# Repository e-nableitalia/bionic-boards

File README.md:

# enable-it Bionic Boards - Third iteration

**This project is part of e-Nable.it Bionic Platform**

An open-source project for developing prosthetic and assistive devices through frugal innovation, designed to be part of e-Nable's open-source prosthetics. The project focuses on building electronic solutions that enable mechanical devices to achieve advanced functionalities, enhancing the community's designs with sophisticated, human-integrated electronic control while maintaining simplicity, affordability, and accessibility.

This project is developed and maintained by the volunteers of the e-Nable Italia community. Our group consists of passionate individuals, including biomedical engineers, mechatronics engineers, and makers, who collaborate to create innovative and accessible solutions. Through our collective efforts, we aim to empower users with open-source, affordable, and customizable assistive devices.

Additional details and information about the **e-nable.it Bionic Platform** can be found in [e-nable.it Bionic Plaform Wiki](https://dev.e-nableitalia.it/wiki/spaces/enableit/pages/360468/Bionic+Workgroup).

# Project roadmap

The project unfolds in three development iterations, each aimed at validating, prototyping, and engineering innovative solutions for low-cost bionic devices.

1. Ideas Validation
The first phase involves conducting experiments and tests to validate initial ideas. This phase focuses on identifying the most promising solutions, exploring various options for controlling actuators and sensors, and collecting data to establish guidelines for the prototype.

2. Prototyping & Custom Solutions
During the prototyping phase, custom solutions are developed using commercial components integrated with specialized electronic boards. The most promising ideas are implemented into physical prototypes to validate architectural and structural concepts. The focus is on simplicity and reliability, ensuring the solutions can be easily replicated and adapted for various bionic devices.

3. Frugal Innovation Engineering
The final phase focuses on engineering the solutions based on frugal innovation principles. Prototypes are optimized to make them accessible, scalable, and practical, with a strong emphasis on cost-effectiveness and real-world applicability. The engineering process also involves creating an open-source hardware platform that enables the creation of modular systems easily combined to build bionic devices.

This repository relates to Iteration #3.

The objective of this iteration is to develop the first reusable deliverables of the project, a set of electronic modules that empower mechanical devices with advanced functionalities. 

By integrating sophisticated, human-centered electronic control, we strive to enhance the capabilities of the e-Nable community's designs while ensuring they remain simple, affordable, and accessible.

> [!CAUTION]
> **The boards published in this repository are still under development and, until fully completed and thoroughly validated, they are intended solely as technological demonstrators and are not designed for practical use.**

## Initial Release Boards

This initial release includes the following boards:

**1. Bionic Controller**  
The Bionic Controller is a custom control board designed to house and expand the capabilities of the M5Stack Atom S3 board. It connects seamlessly to its daughter boards via an 8+8 pin expansion slot.

**This module serves as the foundation for flexible, low-cost prosthetic and assistive device applications.**

Key features:  
- **Size:** 25x50mm  
- **Layers:** 2-layer board  
- **Power Management:** Provides battery management and charging, delivering three power outputs (+3.3V, +5V, and a variable voltage between 5V and 12V for powering multiple motors simultaneously).  
- **Expansion Slot:** Includes a 8+8 pin expansion slot for a daughter board.  
- **Housing:** Designed to house the [M5Stack Atom S3](https://docs.m5stack.com/en/core/AtomS3) board.  

Latest version:
- **Files:** Atom S3 Module Rev. D

**2. ActuatorSense Module**  
The ActuatorSense module is a compact, low-cost H-bridge/waveshare motor controller daughter board designed to connect seamlessly to the expansion slot of the Bionic Controller board.

Key features:  
- **Size:** 26x25mm  
- **Layers:** 2-layer board  
- **Capabilities:**  
  - Can control up to two linear actuators (or two motors).
  - Can control waveshare servo/motors  
  - Supports a combination of one actuator/motor and one sensor (myoelectric or pressure). 

Latest version:
- **Files:** DRV8441A Module Rev B  

**3. Advanced Control Board**  
An enhanced version of the basic control board with added features (not yet released):  
- Includes three slots for daughter boards, enabling control of multiple actuators.  
- Retains all capabilities of the Bionic Controller.  

**4. Daughter Board with TI ADS1298**  
A specialized board for EMG signal acquisition (previous version prototype available):  
- **Functionality:** Designed to acquire up to eight simultaneous myoelectric signals.

## Project updates
250110 - Initial file upload

250113 - Updated to latest release, changes:
- fixed mechanical issue (wrong housing position for Atom S3 board, moved the connectors 4.5 mm below)
- reworked board polygons (cleaner design)
- completed 3d board models
- replaced single pin 2.54 headers with wirepad

250724 - Updated to latest release (DRV8441A Module Rev B), changes:
- tilted pin order on Actuonix PQ12 connector (J-A1 & J-A2 pin order need to be inverted because the connector has contacts on the opposite side)
- added waveshare driver logic and connector (1 wire data + GND + PWR)
- added a digital switch to enable waveshare (default) or additional h-bridge control (2nd motor)
- fixed ADC/Digital Atom S3 pin swap error (G38 & G39 cannot be used as ADC)

## KNOWN ISSUES

- Waveshare connector pinout is tilter: **Pin 1 is connected to Pin 3, and Pin 3 is connected to Pin 1**. Double-check wiring before connecting.

## Authors

Alberto Navatta - alberto@e-nableitalia.it / alberto.navatta@gmail.com

e-Nable Italia - info@e-nableitalia.it

Check for further information, updates and information on this and other e-Nable Italia’s projects on our website: [https://e-nableitalia.it/](https://e-nableitalia.it/)

## License

This material is released under *Creative Commons - Attribution - Non-Commercial - Share Alike license*

## LIMITATION OF LIABILITY.
UNDER NO CIRCUMSTANCES AND UNDER NO LEGAL THEORY, WHETHER TORT (INCLUDING NEGLIGENCE), CONTRACT, OR OTHERWISE, SHALL YOU, THE INITIAL DEVELOPER, ANY OTHER CONTRIBUTOR, OR ANY DISTRIBUTOR OF COVERED CODE, OR ANY SUPPLIER OF ANY OF SUCH PARTIES, BE LIABLE TO ANY PERSON FOR ANY INDIRECT, SPECIAL, INCIDENTAL, OR CONSEQUENTIAL DAMAGES OF ANY CHARACTER INCLUDING, WITHOUT LIMITATION, DAMAGES FOR LOSS OF GOODWILL, WORK STOPPAGE, COMPUTER FAILURE OR MALFUNCTION, OR ANY AND ALL OTHER COMMERCIAL DAMAGES OR LOSSES, EVEN IF SUCH PARTY SHALL HAVE BEEN INFORMED OF THE POSSIBILITY OF SUCH DAMAGES. THIS LIMITATION OF LIABILITY SHALL NOT APPLY TO LIABILITY FOR DEATH OR PERSONAL INJURY RESULTING FROM SUCH PARTY'S NEGLIGENCE TO THE EXTENT APPLICABLE LAW PROHIBITS SUCH LIMITATION. SOME JURISDICTIONS DO NOT ALLOW THE EXCLUSION OR LIMITATION OF INCIDENTAL OR CONSEQUENTIAL DAMAGES, SO THIS EXCLUSION AND LIMITATION MAY NOT APPLY TO YOU.

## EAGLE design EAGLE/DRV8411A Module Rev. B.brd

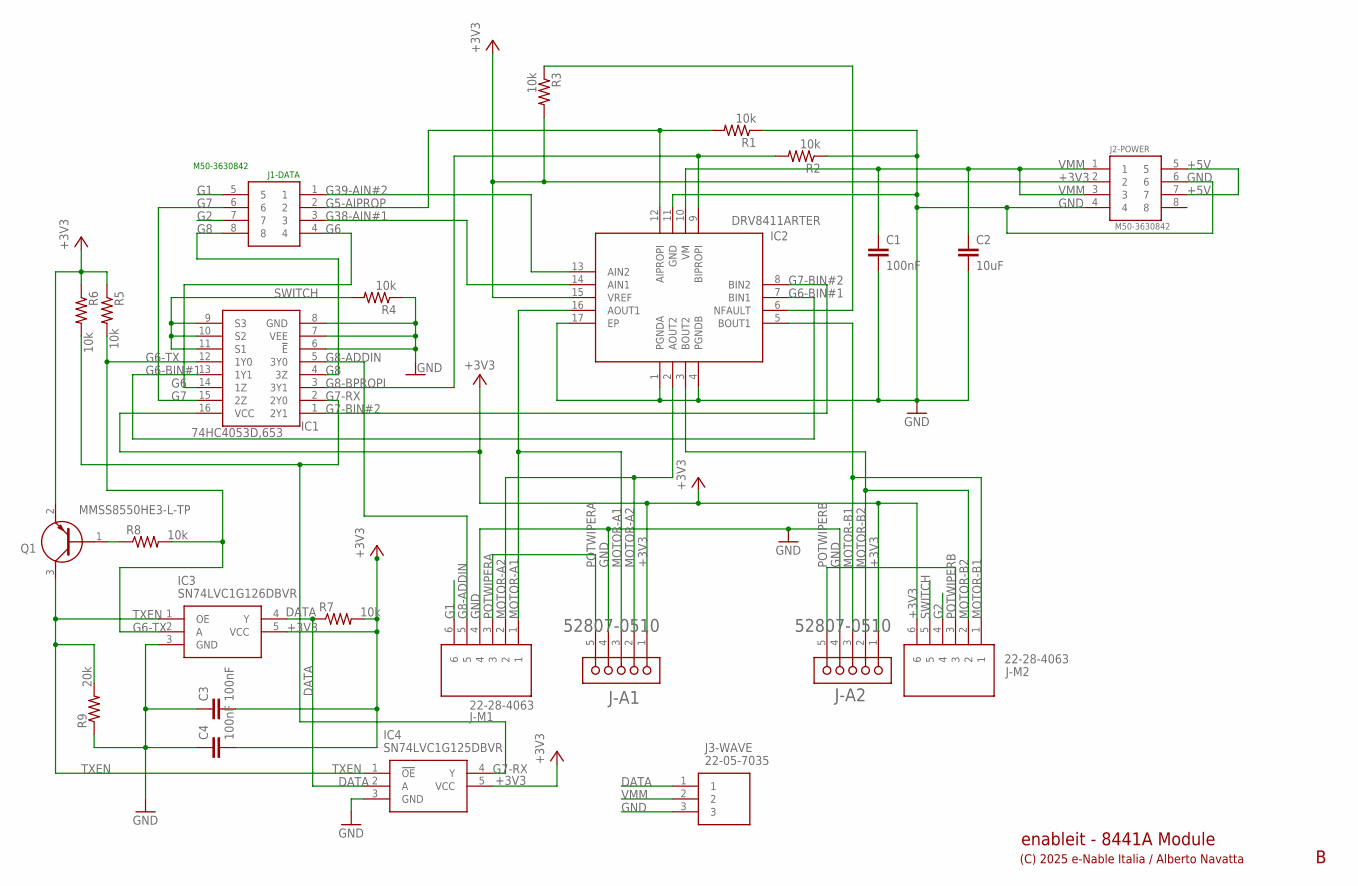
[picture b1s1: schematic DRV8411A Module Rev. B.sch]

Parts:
C1, C3, C4: 100nF; C0603
C2: 10uF; C1206
IC1: 74HC4053D,653; SOIC127P600X175-16N
IC2: DRV8411ARTER; QFN50P300X300X80-17N
IC3: SN74LVC1G126DBVR; SOT95P280X145-5N
IC4: SN74LVC1G125DBVR; SOT95P280X145-5N
J1-DATA, J2-POWER: M50-3630842; HUSRSP8W42P127_1016X210X430P
J3-WAVE: 22-05-7035; SHDRRA3W60P0X250_1X3_990X790X4
J-A1, J-A2: MOLEX_52807-0510MOLEX_52807-0510_0_0; MOLEX_52807-0510_0
J-M1, J-M2: 22-28-4063; HDRV6W66P0X254_1X6_1524X249X83
Q1: MMSS8550HE3-L-TP; SOT95P237X125-3N
R1, R2, R3, R4, R5, R6, R7, R8: 10k; R1206
R9: 20k; R1206

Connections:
+3V3: C3.2, C4.2, IC1.16 (VCC), IC2.15 (VREF), IC3.5 (VCC), IC4.5 (VCC), J2-POWER.2, J-A1.1, J-A2.1, J-M2.6, Q1.2 (E), R3.2, R5.1, R6.1, R7.2
+5V: J2-POWER.5, J2-POWER.7
DATA: IC3.4 (Y), IC4.2 (A), J3-WAVE.1, R7.1
G1: J1-DATA.5, J-M1.6
G2: J1-DATA.7, J-M2.4
G5-AIPROP: IC2.12 (AIPROPI), J1-DATA.2, R1.2
G6: IC1.14 (1Z), J1-DATA.4
G6-BIN#1: IC1.13 (1Y1), IC2.7 (BIN1)
G6-TX: IC1.12 (1Y0), IC3.2 (A), R5.2, R8.2
G7: IC1.15 (2Z), J1-DATA.6
G7-BIN#2: IC1.1 (2Y1), IC2.8 (BIN2)
G7-RX: IC1.2 (2Y0), IC4.4 (Y), R6.2
G8: IC1.4 (3Z), J1-DATA.8
G8-ADDIN: IC1.5 (3Y0), J-M1.5
G8-BPROPI: IC1.3 (3Y1), IC2.9 (BIPROPI), R2.2
G38-AIN#1: IC2.14 (AIN1), J1-DATA.3
G39-AIN#2: IC2.13 (AIN2), J1-DATA.1
GND: C1.2, C2.2, C3.1, C4.1, IC1.6 (!E), IC1.7 (VEE), IC1.8 (GND), IC2.1 (PGNDA), IC2.4 (PGNDB), IC2.11 (GND), IC2.17 (EP), IC3.3 (GND), IC4.3 (GND), J2-POWER.4, J2-POWER.6, J3-WAVE.3, J-A1.4, J-A2.4, J-M1.4, R1.1, R2.1, R4.1, R9.1
MOTOR-A1: IC2.16 (AOUT1), J-A1.3, J-M1.1
MOTOR-A2: IC2.2 (AOUT2), J-A1.2, J-M1.2
MOTOR-B1: IC2.5 (BOUT1), J-A2.3, J-M2.1
MOTOR-B2: IC2.3 (BOUT2), J-A2.2, J-M2.2
unnamed: Q1.1 (B), R8.1
NFAULT: IC2.6 (NFAULT), R3.1
POTWIPERA: J-A1.5, J-M1.3
POTWIPERB: J-A2.5, J-M2.3
SWITCH: IC1.9 (S3), IC1.10 (S2), IC1.11 (S1), J-M2.5, R4.2
TXEN: IC3.1 (OE), IC4.1 (!OE), Q1.3 (C), R9.2
VMM: C1.1, C2.1, IC2.10 (VM), J2-POWER.1, J2-POWER.3, J3-WAVE.2

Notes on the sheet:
(C) 2025 e-Nable Italia / Alberto Navatta
enableit - 8441A Module

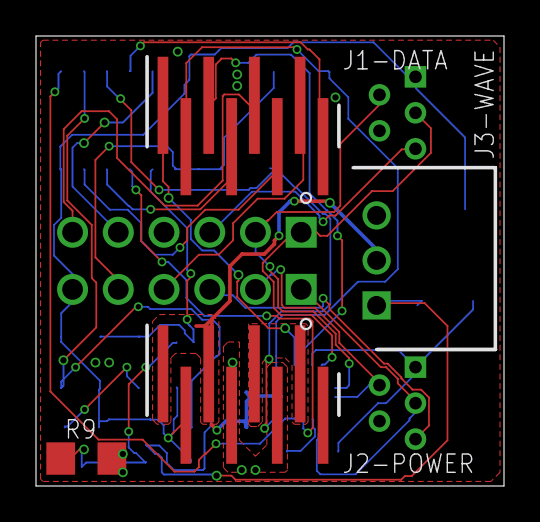
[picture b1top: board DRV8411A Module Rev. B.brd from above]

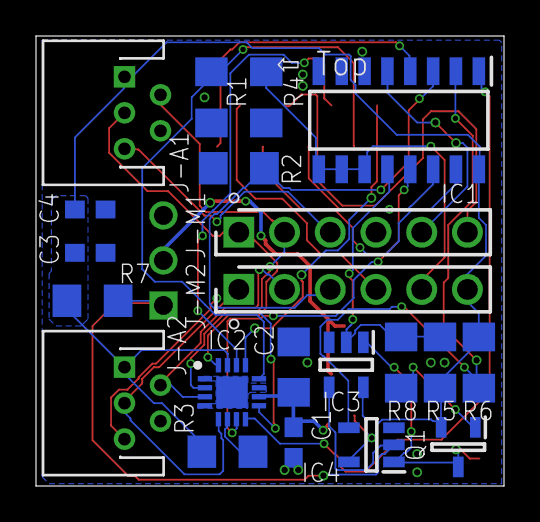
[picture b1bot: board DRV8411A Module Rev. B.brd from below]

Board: 2 copper layers, 26.0 x 25.0 mm, 25 parts (21 on the bottom side), 29 nets.

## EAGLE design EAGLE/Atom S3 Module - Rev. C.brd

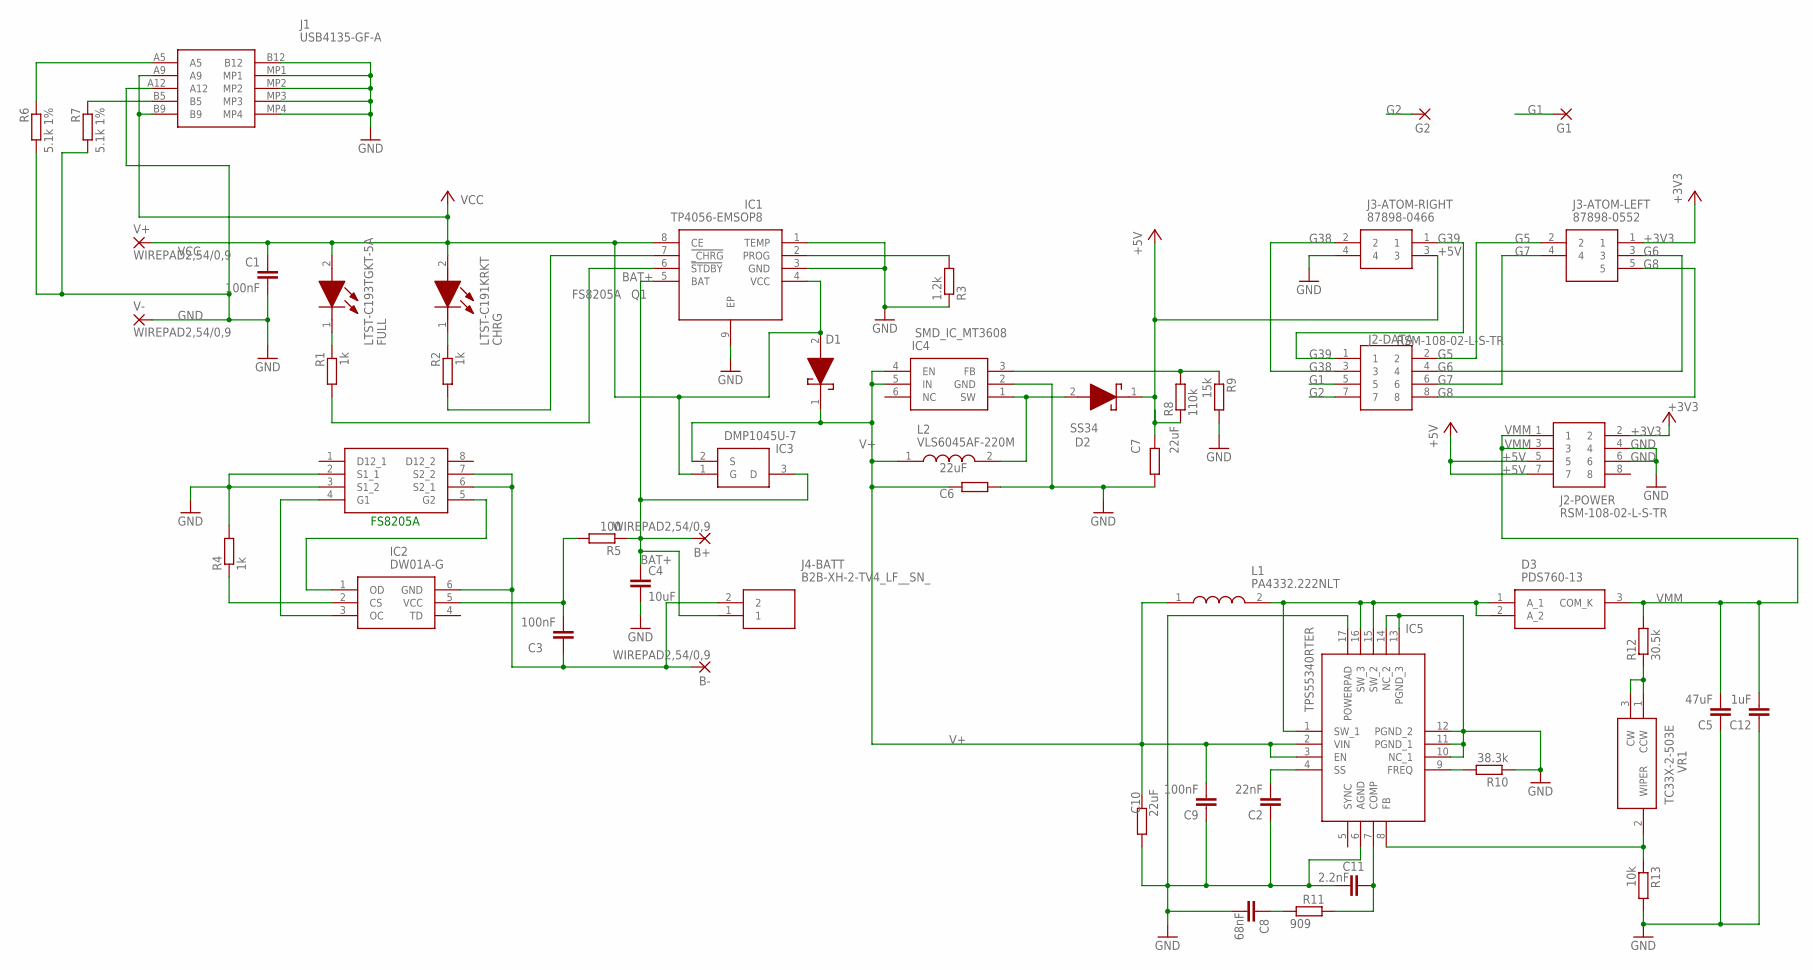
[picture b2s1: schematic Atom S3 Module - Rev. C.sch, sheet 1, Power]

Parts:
B+: WIREPAD2,54/0,9; 2,54/0,9
B-: WIREPAD2,54/0,9; 2,54/0,9
C1, C3, C9: 100nF; C0603
C2: 22nF; C0603
C4: 10uF; C0603
C5: 47uF; C1210
C6, C7, C10: 22uF; R0805
C8: 68nF; C0603
C11: 2.2nF; C0603
C12: 1uF; C0603
CHRG: LTST-C191KRKT; LEDC1608X55N
D1, D2: SS34; DIOM8059X256N
D3: PDS760-13; PDS76013
FULL: LTST-C193TGKT-5A; LEDC1608X45N
G1, G2: WIREPAD1,6/0,9; 1,6/0,9
IC1: TP4056-EMSOP8; SOP65P490X110-9N
IC2: DW01A-G; SOT95P190X145-6N
IC3: DMP1045U-7; SOT96P240X110-3N
IC4: SMD_IC_MT3608; SOT95P280X145-6N
IC5: TPS55340RTER; QFN50P300X300X80-17N
J1: USB4135-GF-A; USB4135GFA
J2-DATA, J2-POWER: RSM-108-02-L-S-TR; RSM10802LSTR
J3-ATOM-LEFT: 87898-0552; 878980552
J3-ATOM-RIGHT: 87898-0466; 878980466
J4-BATT: B2B-XH-2-TV4_LF__SN_; B2BXH2TV4LFSN
L1: PA4332.222NLT; INDPM4042X200N
L2: VLS6045AF-220M; VLS6045
Q1: FS8205A; SOP65P640X120-8N
R1, R2, R4: 1k; R0603
R3: 1.2k; R0603
R5: 100; R0603
R6, R7: 5.1k 1%; R0603
R8: 110k; R0603
R9: 15k; R0603
R10: 38.3k; R0603
R11: 909; R0603
R12: 30.5k; R0805
R13: 10k; R0603
V+: WIREPAD2,54/0,9; 2,54/0,9
V-: WIREPAD2,54/0,9; 2,54/0,9
VR1: TC33X-2-503E; TC33X2503E

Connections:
+3V3: J2-POWER.2, J3-ATOM-LEFT.1
+5V: C7.2, D2.1 (K), J2-POWER.5, J2-POWER.7, J3-ATOM-RIGHT.3, R8.1
BAT+: B+.1, C4.1, IC1.5 (BAT), IC3.3 (D), J4-BATT.1, R5.1
BAT-: B-.1, C3.1, IC2.6 (GND), J4-BATT.2, Q1.6 (S2_1), Q1.7 (S2_2)
G1: G1.1, J2-DATA.5
G2: G2.1, J2-DATA.7
G5: J2-DATA.2, J3-ATOM-LEFT.2
G6: J2-DATA.4, J3-ATOM-LEFT.3
G7: J2-DATA.6, J3-ATOM-LEFT.4
G8: J2-DATA.8, J3-ATOM-LEFT.5
G38: J2-DATA.3, J3-ATOM-RIGHT.2
G39: J2-DATA.1, J3-ATOM-RIGHT.1
GND: C1.2, C2.1, C4.2, C5.1, C6.1, C7.1, C8.2, C9.1, C10.1, C11.2, C12.1, IC1.1 (TEMP), IC1.3 (GND), IC1.9 (EP), IC4.2 (GND), IC5.6 (AGND), IC5.10 (NC_1), IC5.11 (PGND_1), IC5.12 (PGND_2), IC5.13 (PGND_3), IC5.14 (NC_2), IC5.17 (POWERPAD), J1.A12, J1.B12, J1.MP1, J1.MP2, J1.MP3, J1.MP4, J2-POWER.4, J2-POWER.6, J3-ATOM-RIGHT.4, Q1.2 (S1_1), Q1.3 (S1_2), R3.1, R4.2, R6.2, R7.2, R9.2, R10.1, R13.2, V-.1
unnamed: FULL.1 (K), R1.1
unnamed: CHRG.1 (K), R2.1
unnamed: IC1.6 (!STDBY), R1.2
unnamed: IC1.7 (!_CHRG), R2.2
unnamed: IC2.3 (OC), Q1.4 (G1)
unnamed: J1.B5, R7.1
unnamed: IC1.2 (PROG), R3.2
unnamed: IC2.2 (CS), R4.1
unnamed: IC2.1 (OD), Q1.5 (G2)
unnamed: D2.2 (A), IC4.1 (SW), L2.2
unnamed: C3.2, IC2.5 (VCC), R5.2
unnamed: J1.A5, R6.1
unnamed: IC5.9 (FREQ), R10.2
unnamed: IC4.3 (FB), R8.2, R9.1
unnamed: C11.1, IC5.7 (COMP), R11.2
unnamed: C8.1, R11.1
unnamed: D3.1 (A_1), D3.2 (A_2), IC5.1 (SW_1), IC5.15 (SW_2), IC5.16 (SW_3), L1.2
unnamed: C2.2, IC5.4 (SS)
unnamed: R12.1, VR1.1 (CCW), VR1.3 (CW)
unnamed: IC5.8 (FB), R13.1, VR1.2 (WIPER)
V+: C6.2, C9.2, C10.2, D1.1 (K), IC3.2 (S), IC4.4 (EN), IC4.5 (IN), IC5.2 (VIN), IC5.3 (EN), L1.1, L2.1
VCC: C1.1, CHRG.2 (A), D1.2 (A), FULL.2 (A), IC1.4 (VCC), IC1.8 (CE), IC3.1 (G), J1.A9, J1.B9, V+.1
VMM: C5.2, C12.2, D3.3 (COM_K), J2-POWER.1, J2-POWER.3, R12.2

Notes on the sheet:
FS8205A

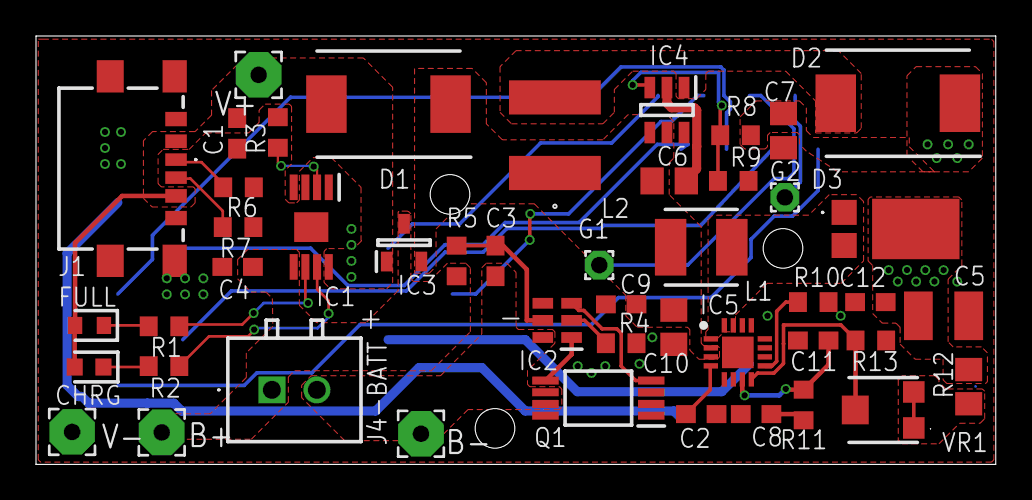
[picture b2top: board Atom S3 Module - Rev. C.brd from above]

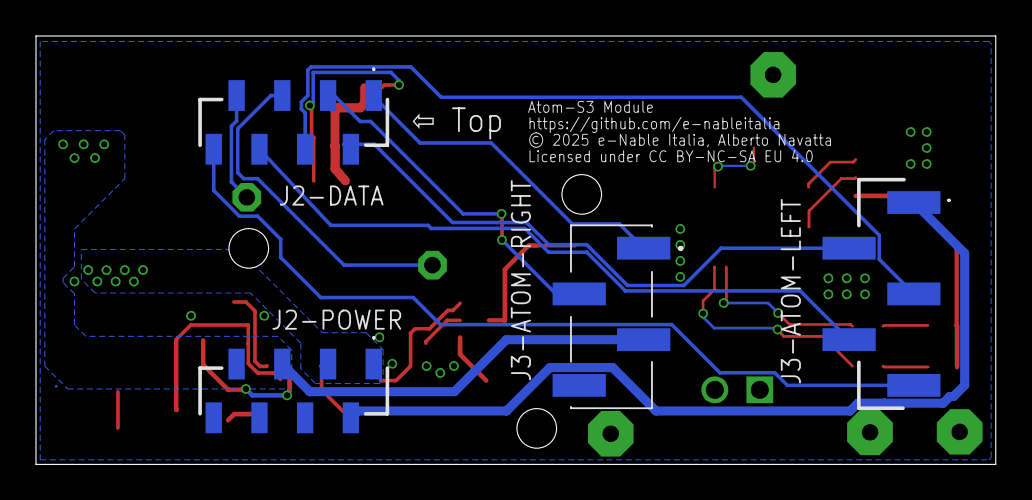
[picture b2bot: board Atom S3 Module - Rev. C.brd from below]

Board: 2 copper layers, 53.3 x 23.8 mm, 51 parts (4 on the bottom side), 36 nets.

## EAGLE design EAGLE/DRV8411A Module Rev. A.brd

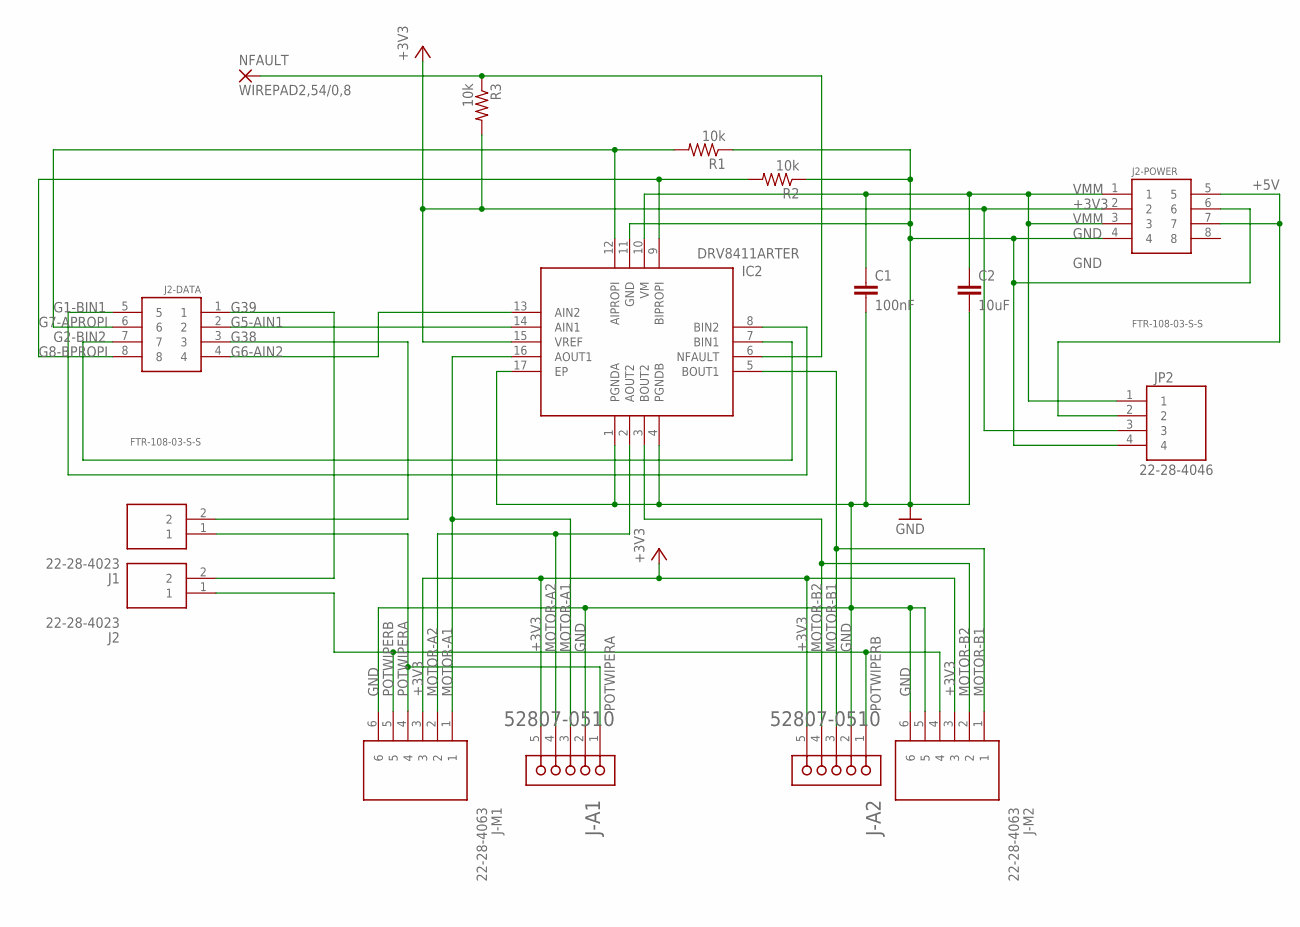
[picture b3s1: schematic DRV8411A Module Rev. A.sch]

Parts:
C1: 100nF; C0603
C2: 10uF; C1206
IC2: DRV8411ARTER; QFN50P300X300X80-17N
J1, J2: 22-28-4023; HDRV2W87P0X254_1X2_508X249X863
J2-DATA, J2-POWER: FTR-108-03-S-S; HUSRSP8W46P127_1016X248X572P
J-A1, J-A2: MOLEX_52807-0510MOLEX_52807-0510_0_0; MOLEX_52807-0510_0
J-M1, J-M2: 22-28-4063; HDRV6W66P0X254_1X6_1524X249X83
JP2: 22-28-4046; HDRV4W66P0X254_1X4_1016X249X83
NFAULT: WIREPAD2,54/0,8; 2,54/0,8
R1, R2, R3: 10k; R1206

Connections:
+3V3: IC2.15 (VREF), J2-POWER.2, J-A1.5, J-A2.5, J-M1.3, J-M2.3, JP2.3, R3.2
+5V: J2-POWER.5, J2-POWER.7, JP2.2
G1-BIN1: IC2.8 (BIN2), J2-DATA.5
G2-BIN2: IC2.7 (BIN1), J2-DATA.7
G5-AIN1: IC2.14 (AIN1), J2-DATA.2
G6-AIN2: IC2.13 (AIN2), J2-DATA.4
G7-APROPI: IC2.12 (AIPROPI), J2-DATA.6, R1.2
G8-BPROPI: IC2.9 (BIPROPI), J2-DATA.8, R2.2
G38: J1.2, J2-DATA.3
G39: J2.2, J2-DATA.1
GND: C1.2, C2.2, IC2.1 (PGNDA), IC2.4 (PGNDB), IC2.11 (GND), IC2.17 (EP), J2-POWER.4, J2-POWER.6, J-A1.2, J-A2.2, J-M1.6, J-M2.5, J-M2.6, JP2.4, R1.1, R2.1
MOTOR-A1: IC2.16 (AOUT1), J-A1.3, J-M1.1
MOTOR-A2: IC2.2 (AOUT2), J-A1.4, J-M1.2
MOTOR-B1: IC2.5 (BOUT1), J-A2.3, J-M2.1
MOTOR-B2: IC2.3 (BOUT2), J-A2.4, J-M2.2
NFAULT: IC2.6 (NFAULT), NFAULT.1, R3.1
POTWIPERA: J1.1, J-A1.1, J-M1.4
POTWIPERB: J2.1, J-A2.1, J-M1.5, J-M2.4
VMM: C1.1, C2.1, IC2.10 (VM), J2-POWER.1, J2-POWER.3, JP2.1

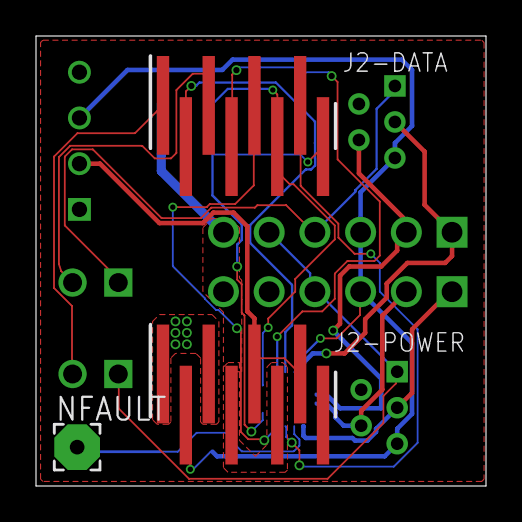
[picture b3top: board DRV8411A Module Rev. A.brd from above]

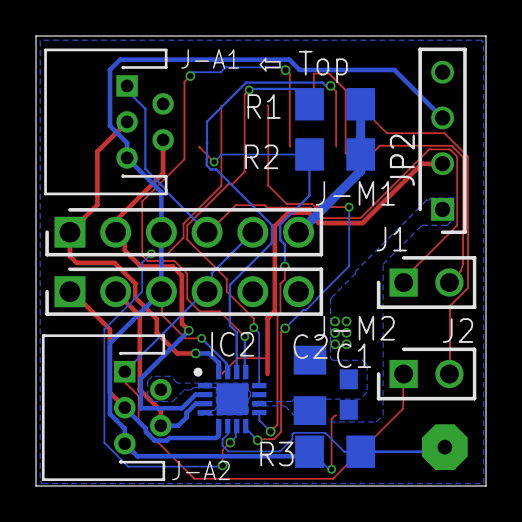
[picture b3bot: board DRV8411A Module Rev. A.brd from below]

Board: 2 copper layers, 25.0 x 25.0 mm, 16 parts (13 on the bottom side), 19 nets.

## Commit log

2025-01-10 repo init, added README
2025-01-10 added first release of BOM, eagle projects and BOM
2025-01-10 added first release of BOM, eagle projects and gerber files
2025-01-12 updated to the latest version, fixed mechanical design to adjust housing of Atom S3 board, added holes for secure mounting
2025-12-07 Update README.md with latest module revisions and features
    - Updated Atom S3 Module to Rev. D
    - Enhanced ActuatorSense module description and updated size
    - Revised latest version of ActuatorSense to Rev. B
    - Clarified features of Advanced Control Board and Daughter Board with TI ADS1298
    - Added new project update for DRV8441A Module Rev B with detailed changes
    - Fixed minor formatting issues and updated contact information
2025-12-07 Update README.md to clarify known issues with Waveshare connector pinout
2025-12-07 Update README.md with correct link to e-nable.it Bionic Platform Wiki

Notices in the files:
EAGLE/Atom S3 Module - Rev. C.brd:
© 2025 e-Nable Italia, Alberto Navatta
Licensed under CC BY-NC-SA EU 4.0
